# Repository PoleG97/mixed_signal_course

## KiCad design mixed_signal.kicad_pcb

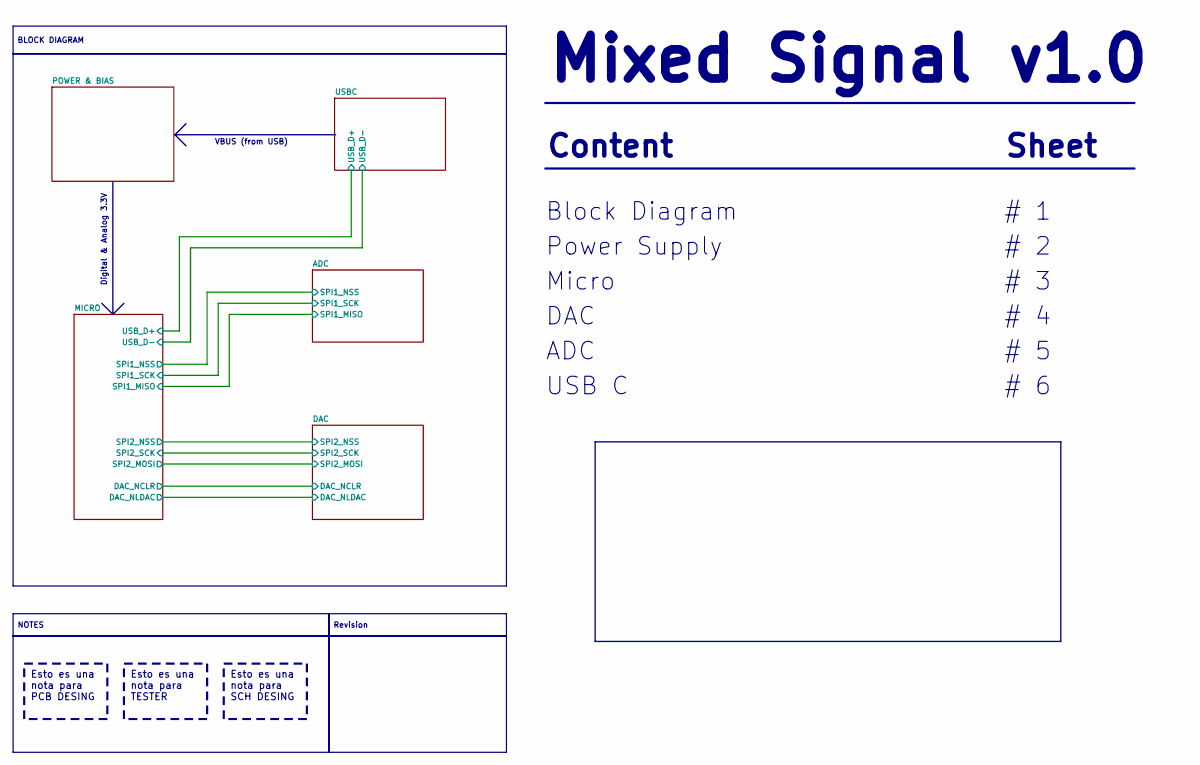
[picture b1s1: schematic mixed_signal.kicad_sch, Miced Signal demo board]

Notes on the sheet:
Micro
# 2
ADC
# 4
Power Supply
# 3
# 1
Content
USB C
v1.0
# 5
VBUS (from USB)
Block Diagram
Mixed Signal
DAC
Digital & Analog 3.3V
# 6
Sheet
Esto es una nota para TESTER
NOTES
Esto es una nota para SCH DESING
BLOCK DIAGRAM
Esto es una nota para PCB DESING
Revision

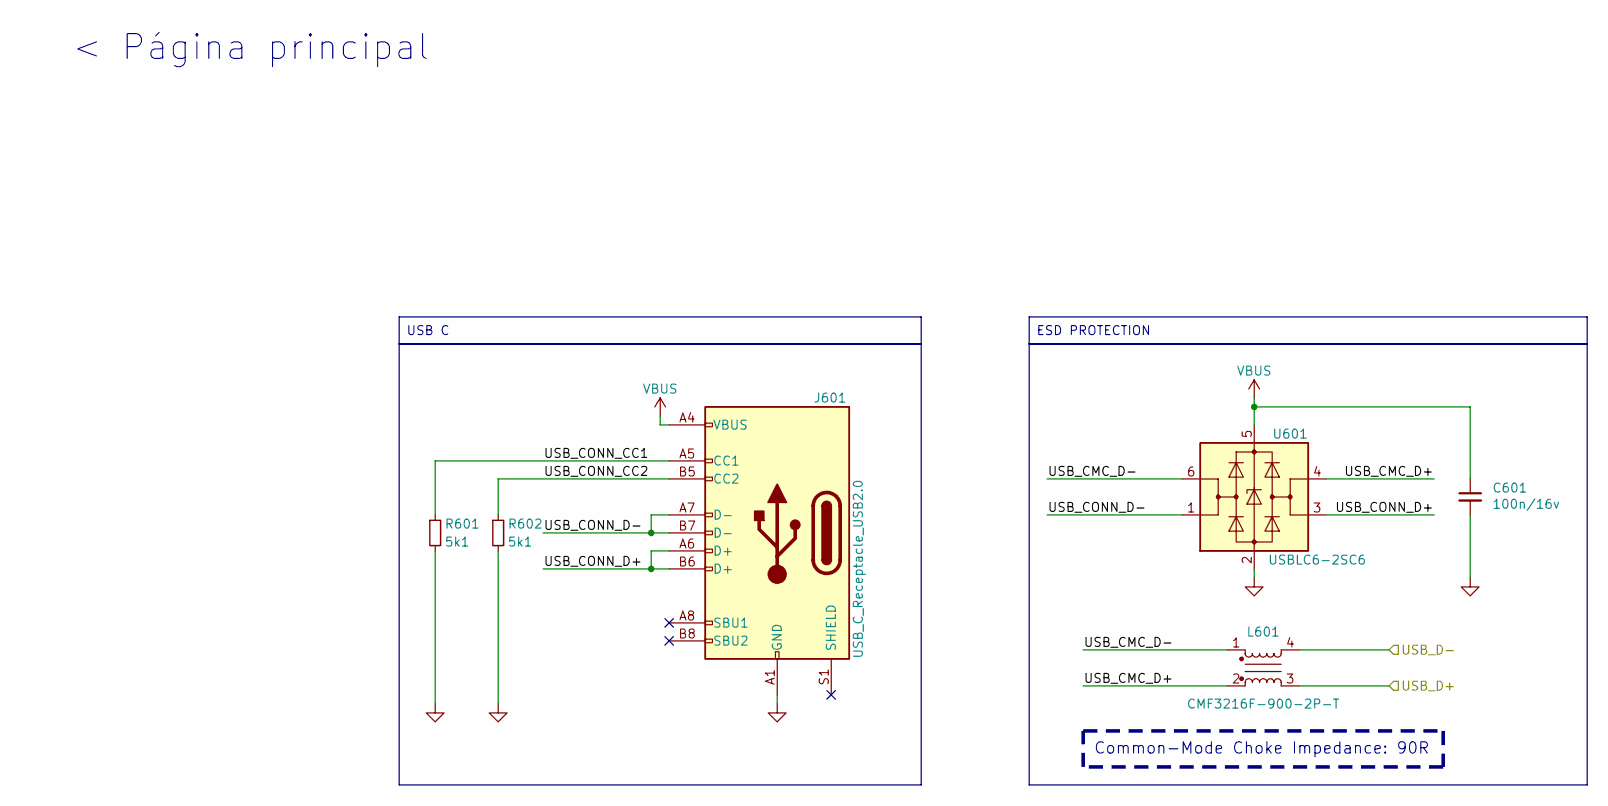
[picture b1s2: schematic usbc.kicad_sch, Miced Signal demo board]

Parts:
C601: 100n/16v; C_0402_1005Metric_Pad0.74x0.62mm_HandSolder; PART_NUMBER GRM155R71C104KA88J
J601: USB_C_Receptacle_USB2.0; USB_C_Receptacle_HRO_TYPE-C-31-M-12
L601: CMF3216F-900-2P-T; CMF3216F
R601, R602: 5k1; R_0402_1005Metric
U601: USBLC6-2SC6; SOT-23-6

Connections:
/MICRO/USB_D+: L601.3; also elsewhere on the board
/MICRO/USB_D-: L601.4; also elsewhere on the board
/USBC/USB_CMC_D+: L601.2, U601.4 (I/O2)
/USBC/USB_CMC_D-: L601.1, U601.6 (I/O1)
/USBC/USB_CONN_CC1: J601.A5 (CC1), R601.1
/USBC/USB_CONN_CC2: J601.B5 (CC2), R602.1
/USBC/USB_CONN_D+: J601.A6 (D+), J601.B6 (D+), U601.3 (I/O2)
/USBC/USB_CONN_D-: J601.A7 (D-), J601.B7 (D-), U601.1 (I/O1)
GND: C601.2, J601.A1 (GND), J601.A12 (GND), J601.B1 (GND), J601.B12 (GND), R601.2, R602.2, U601.2 (GND); also elsewhere on the board
VBUS: C601.1, J601.A4 (VBUS), J601.A9 (VBUS), J601.B4 (VBUS), J601.B9 (VBUS), U601.5 (VBUS); also elsewhere on the board

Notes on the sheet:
Common-Mode Choke Impedance: 90R
< Página principal
ESD PROTECTION
USB C

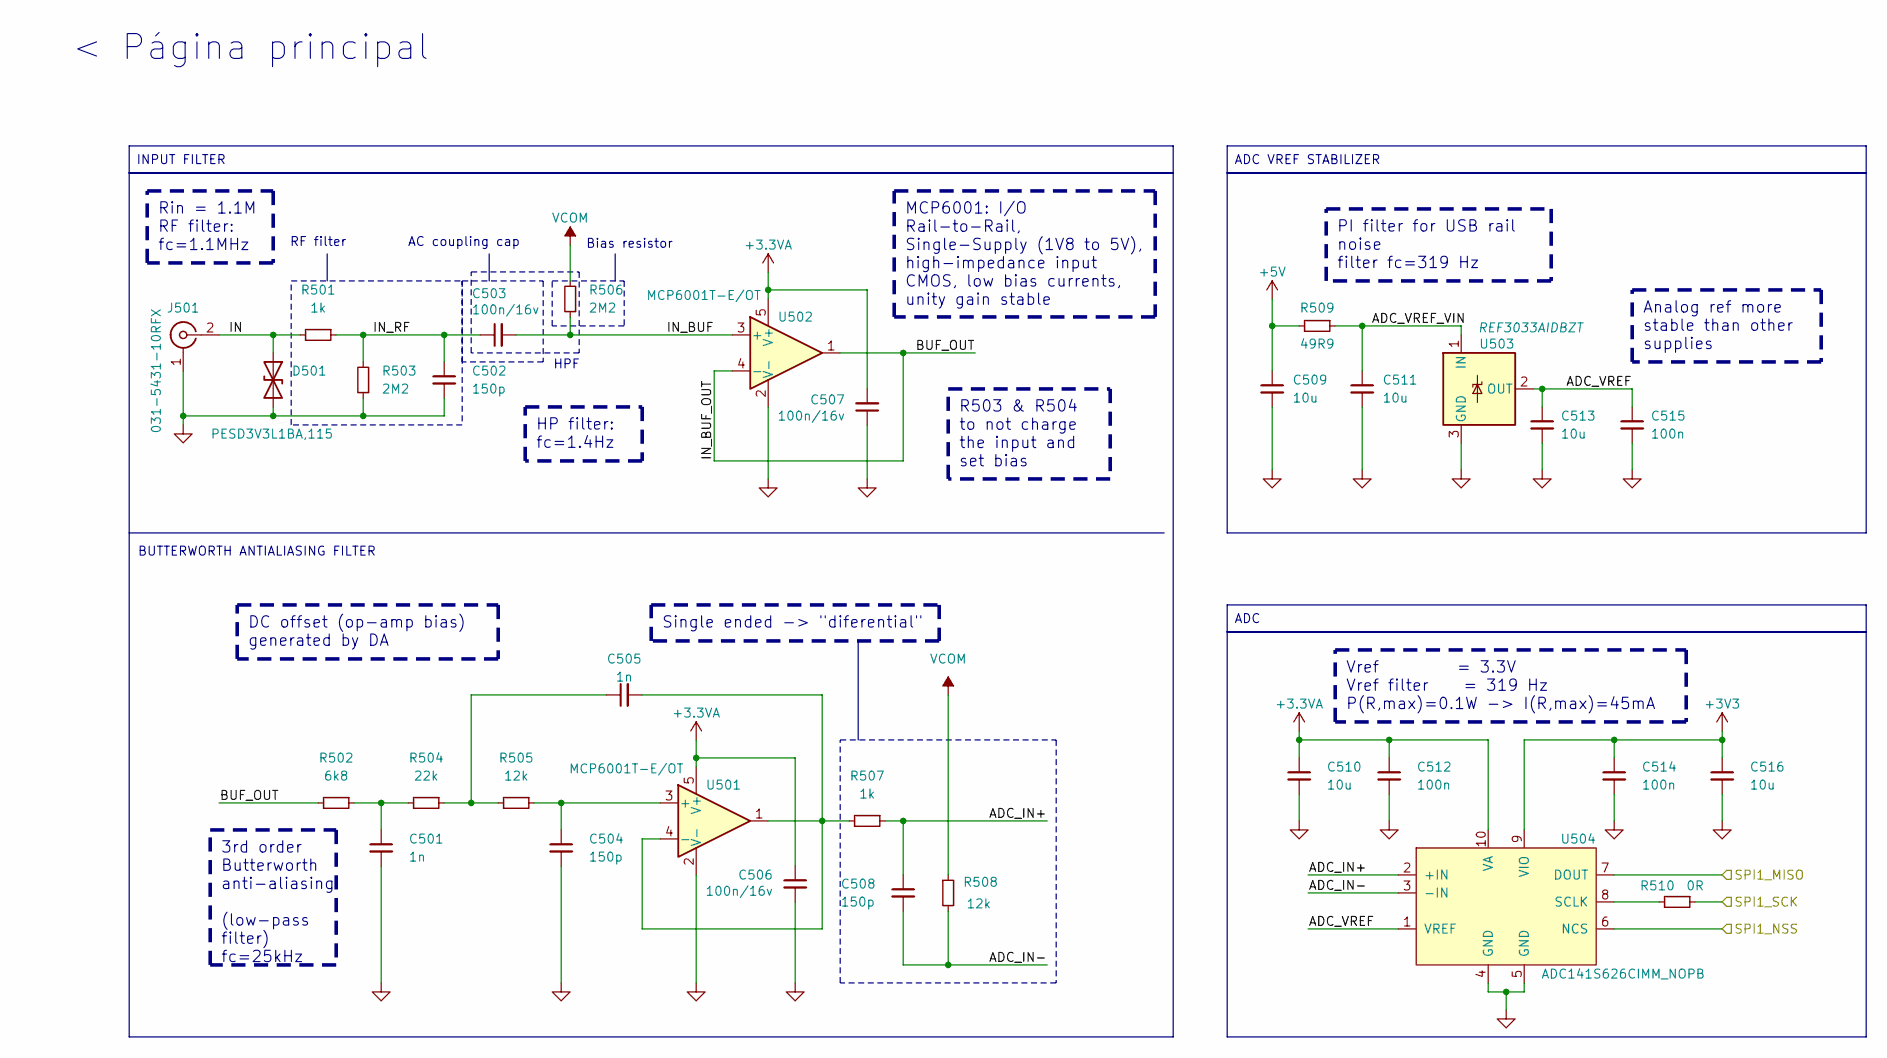
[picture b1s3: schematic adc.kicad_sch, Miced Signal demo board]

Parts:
C501, C505: 1n; C_0402_1005Metric
C502, C504, C508: 150p; C_0402_1005Metric
C503, C506, C507: 100n/16v; C_0402_1005Metric_Pad0.74x0.62mm_HandSolder; PART_NUMBER GRM155R71C104KA88J
C509, C510, C511, C513, C516: 10u; C_0603_1608Metric
C512, C514, C515: 100n; C_0402_1005Metric
D501: PESD3V3L1BA,115; D_SOD-323
J501: 031-5431-10RFX
R501, R507: 1k; R_0402_1005Metric
R502: 6k8; R_0402_1005Metric
R503, R506: 2M2; R_0402_1005Metric
R504: 22k; R_0402_1005Metric
R505, R508: 12k; R_0402_1005Metric
R509: 49R9; R_0402_1005Metric
R510: 0R; R_0402_1005Metric
U501, U502: MCP6001T-E/OT; SOT-23-5
U503: REF3033AIDBZT; SOT-23
U504: ADC141S626CIMM_NOPB; VSSOP-10

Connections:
+3.3VA: C506.1, C507.2, C510.1, C512.1, U501.5 (V+), U502.5 (V+), U504.10 (VA); also elsewhere on the board
+3V3: C514.1, C516.1, U504.9 (VIO); also elsewhere on the board
+5V: C509.1, R509.2; also elsewhere on the board
/ADC/ADC_IN+: C508.1, R507.1, U504.2 (+IN)
/ADC/ADC_IN-: C508.2, R508.2, U504.3 (-IN)
/ADC/ADC_VREF: C513.1, C515.1, U503.2 (OUT), U504.1 (VREF)
/ADC/ADC_VREF_VIN: C511.1, R509.1, U503.1 (IN)
/ADC/BUF_OUT: R502.2, U502.1, U502.4 (-)
/ADC/IN: D501.1 (A1), J501.2 (Ext), R501.2
/ADC/IN_BUF: C503.2, R506.1, U502.3 (+)
/ADC/IN_RF: C502.1, C503.1, R501.1, R503.2
/ADC/SPI1_MISO: U504.7 (DOUT); also elsewhere on the board
/ADC/SPI1_NSS: U504.6 (NCS); also elsewhere on the board
/ADC/SPI1_SCK: R510.1; also elsewhere on the board
GND: C501.2, C502.2, C504.2, C506.2, C507.1, C509.2, C510.2, C511.2, C512.2, C513.2, C514.2, C515.2, C516.2, D501.2 (A2), J501.1 (In), R503.1, U501.2 (V-), U502.2 (V-), U503.3 (GND), U504.4 (GND), U504.5 (GND); also elsewhere on the board
unnamed: C501.1, R502.1, R504.2
unnamed: C505.1, R504.1, R505.2
unnamed: C504.1, R505.1, U501.3 (+)
unnamed: C505.2, R507.2, U501.1, U501.4 (-)
unnamed: R510.2, U504.8 (SCLK)
VCOM: R506.2, R508.1; also elsewhere on the board

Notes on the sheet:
RF filter
AC coupling cap
HPF
BUTTERWORTH ANTIALIASING FILTER
Bias resistor
ADC
Vref = 3.3V Vref filter = 319 Hz P(R,max)=0.1W -> I(R,max)=45mA
HP filter: fc=1.4Hz
INPUT FILTER
ADC VREF STABILIZER
Single ended -> "diferential"
MCP6001: I/O Rail-to-Rail, Single-Supply (1V8 to 5V), high-impedance input CMOS, low bias currents, unity gain stable
PI filter for USB rail noise filter fc=319 Hz
Rin = 1.1M RF filter: fc=1.1MHz
DC offset (op-amp bias) generated by DA
3rd order Butterworth anti-aliasing (low-pass filter) fc=25kHz
Analog ref more stable than other supplies
R503 & R504 to not charge the input and set bias
< Página principal

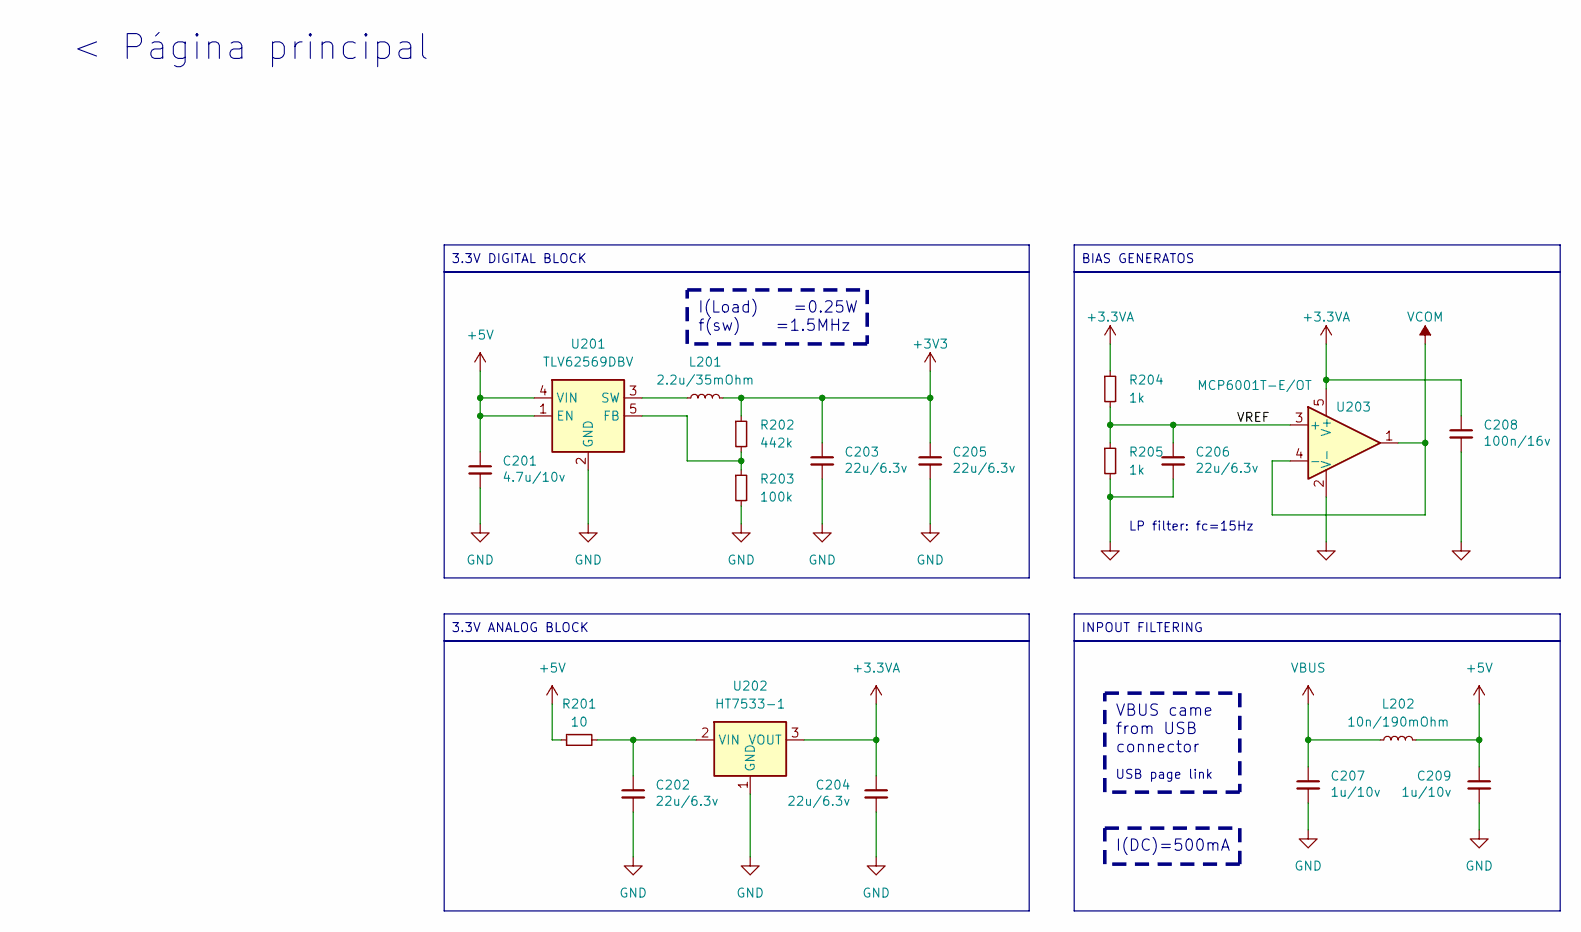
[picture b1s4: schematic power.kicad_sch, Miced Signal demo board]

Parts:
C201: 4.7u/10v; C_0402_1005Metric_Pad0.74x0.62mm_HandSolder; PART_NUMBER C1005X5R1A475K050BC
C202, C203, C204, C205, C206: 22u/6.3v; C_0402_1005Metric_Pad0.74x0.62mm_HandSolder; PART_NUMBER GRJ155R60J106ME11D
C207, C209: 1u/10v; C_0402_1005Metric_Pad0.74x0.62mm_HandSolder; PART_NUMBER CL05B104KP5NNNC
C208: 100n/16v; C_0402_1005Metric_Pad0.74x0.62mm_HandSolder; PART_NUMBER GRM155R71C104KA88J
L201: 2.2u/35mOhm; IND_ASPI-0530HI-2R2M-T2; PART_NUMBER ASPI-0530HI-2R2M-T2
L202: 10n/190mOhm; L_0402_1005Metric_Pad0.77x0.64mm_HandSolder; PART_NUMBER LQG15WZ10NH02D
R201: 10; R_1206_3216Metric_Pad1.30x1.75mm_HandSolder; PART_NUMBER Susumu
R202: 442k; R_0402_1005Metric
R203: 100k; R_0402_1005Metric
R204, R205: 1k; R_0402_1005Metric; PART_NUMBER ERJ-2RKF1001X
U201: TLV62569DBV; SOT-23-5
U202: HT7533-1; SOT-89-3
U203: MCP6001T-E/OT; SOT-23-5; PART_NUMBER MCP6001T-E/OT

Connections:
+3.3VA: C204.1, C208.1, R204.1, U202.3 (VOUT), U203.5 (V+); also elsewhere on the board
+3V3: C203.1, C205.1, L201.2, R202.1; also elsewhere on the board
+5V: C201.1, C209.1, L202.2, R201.1, U201.1 (EN), U201.4 (VIN); also elsewhere on the board
/POWER & BIAS/VREF: C206.1, R204.2, R205.1, U203.3 (+)
GND: C201.2, C202.2, C203.2, C204.2, C205.2, C206.2, C207.2, C208.2, C209.2, R203.2, R205.2, U201.2 (GND), U202.1 (GND), U203.2 (V-); also elsewhere on the board
unnamed: R202.2, R203.1, U201.5 (FB)
unnamed: L201.1, U201.3 (SW)
unnamed: C202.1, R201.2, U202.2 (VIN)
VBUS: C207.1, L202.1; also elsewhere on the board
VCOM: U203.1, U203.4 (-); also elsewhere on the board

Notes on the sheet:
LP filter: fc=15Hz
USB page link
3.3V DIGITAL BLOCK
< Página principal
BIAS GENERATOS
3.3V ANALOG BLOCK
VBUS came from USB connector
I(DC)=500mA
INPOUT FILTERING
I(Load) =0.25W f(sw) =1.5MHz

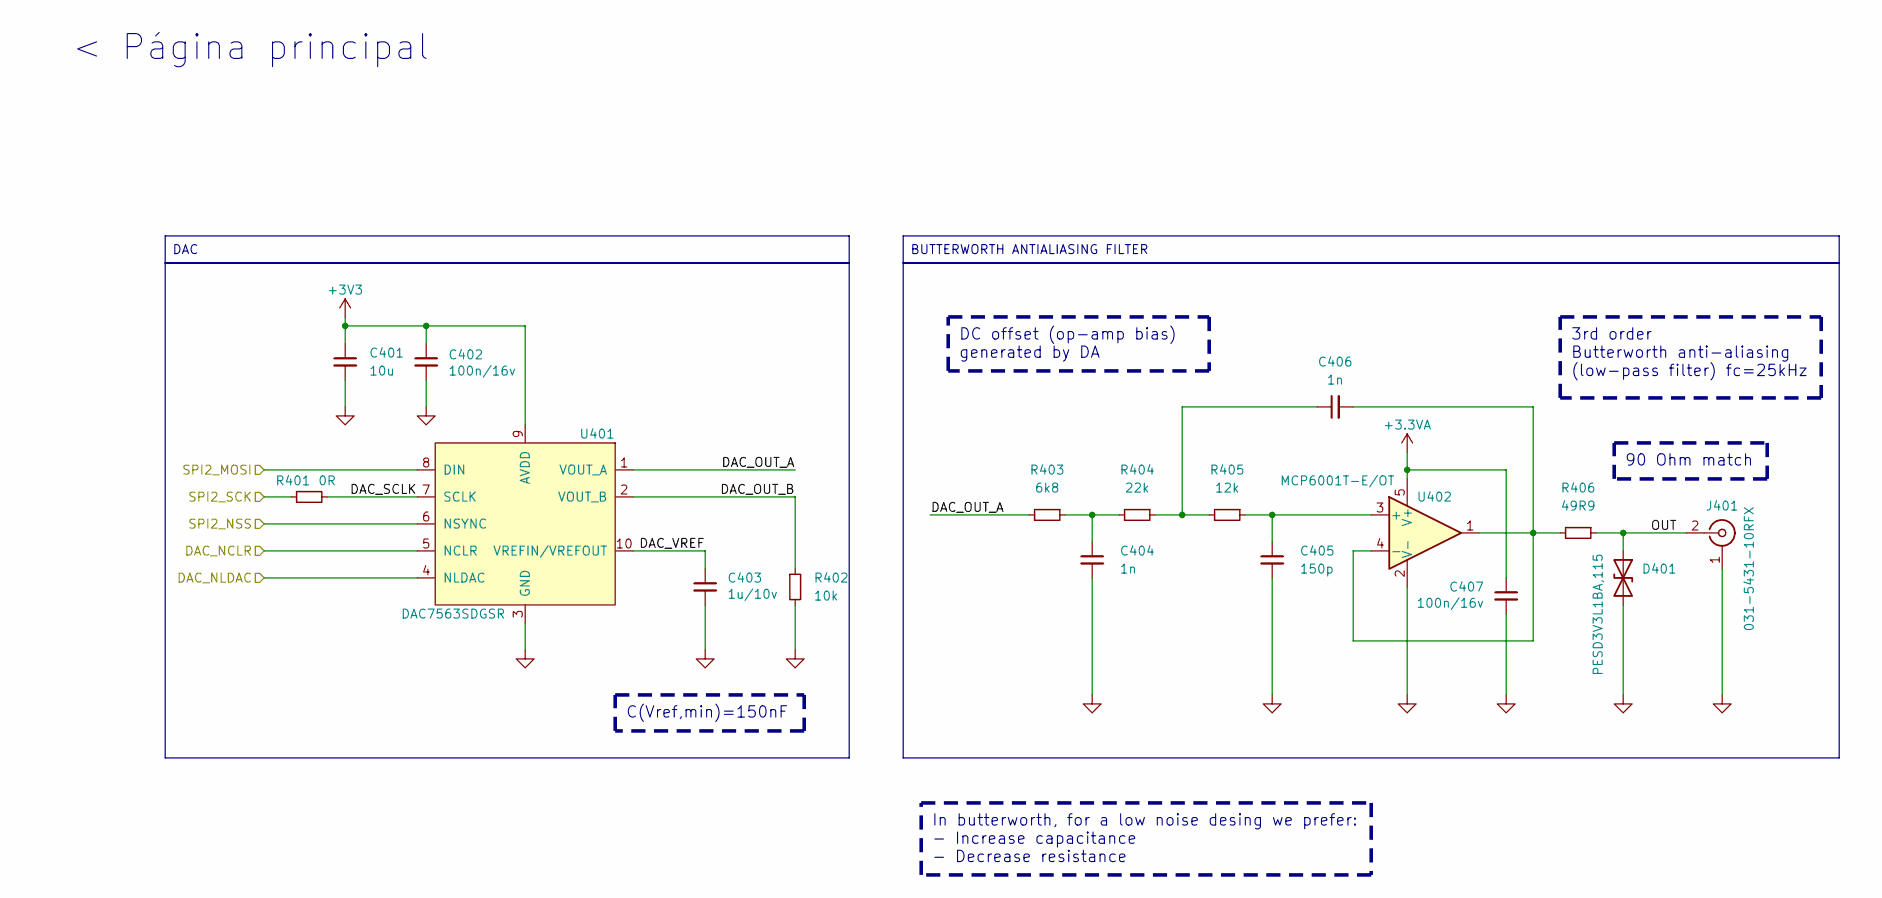
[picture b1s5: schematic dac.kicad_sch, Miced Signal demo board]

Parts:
C401: 10u; C_0603_1608Metric
C402, C407: 100n/16v; C_0402_1005Metric_Pad0.74x0.62mm_HandSolder; PART_NUMBER GRM155R71C104KA88J
C403: 1u/10v; C_0402_1005Metric_Pad0.74x0.62mm_HandSolder; PART_NUMBER CL05B104KP5NNNC
C404, C406: 1n; C_0402_1005Metric
C405: 150p; C_0402_1005Metric
D401: PESD3V3L1BA,115; D_SOD-323
J401: 031-5431-10RFX
R401: 0R; R_0402_1005Metric
R402: 10k; R_0402_1005Metric
R403: 6k8; R_0402_1005Metric
R404: 22k; R_0402_1005Metric
R405: 12k; R_0402_1005Metric
R406: 49R9; R_0402_1005Metric
U401: DAC7563SDGSR; VSSOP-10
U402: MCP6001T-E/OT; SOT-23-5

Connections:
+3.3VA: C407.1, U402.5 (V+); also elsewhere on the board
+3V3: C401.1, C402.1, U401.9 (AVDD); also elsewhere on the board
/DAC/DAC_NCLR: U401.5 (NCLR); also elsewhere on the board
/DAC/DAC_NLDAC: U401.4 (NLDAC); also elsewhere on the board
/DAC/DAC_OUT_A: R403.2, U401.1 (VOUT_A)
/DAC/DAC_OUT_B: R402.1, U401.2 (VOUT_B)
/DAC/DAC_SCLK: R401.2, U401.7 (SCLK)
/DAC/DAC_VREF: C403.1, U401.10 (VREFIN/VREFOUT)
/DAC/OUT: D401.1 (A1), J401.2 (Ext), R406.1
/DAC/SPI2_MOSI: U401.8 (DIN); also elsewhere on the board
/DAC/SPI2_NSS: U401.6 (NSYNC); also elsewhere on the board
/DAC/SPI2_SCK: R401.1; also elsewhere on the board
GND: C401.2, C402.2, C403.2, C404.2, C405.2, C407.2, D401.2 (A2), J401.1 (In), R402.2, U401.3 (GND), U402.2 (V-); also elsewhere on the board
unnamed: C404.1, R403.1, R404.2
unnamed: C406.1, R404.1, R405.2
unnamed: C405.1, R405.1, U402.3 (+)
unnamed: C406.2, R406.2, U402.1, U402.4 (-)

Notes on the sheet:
< Página principal
DAC
In butterworth, for a low noise desing we prefer: - Increase capacitance - Decrease resistance
C(Vref,min)=150nF
DC offset (op-amp bias) generated by DA
BUTTERWORTH ANTIALIASING FILTER
90 Ohm match
3rd order Butterworth anti-aliasing (low-pass filter) fc=25kHz

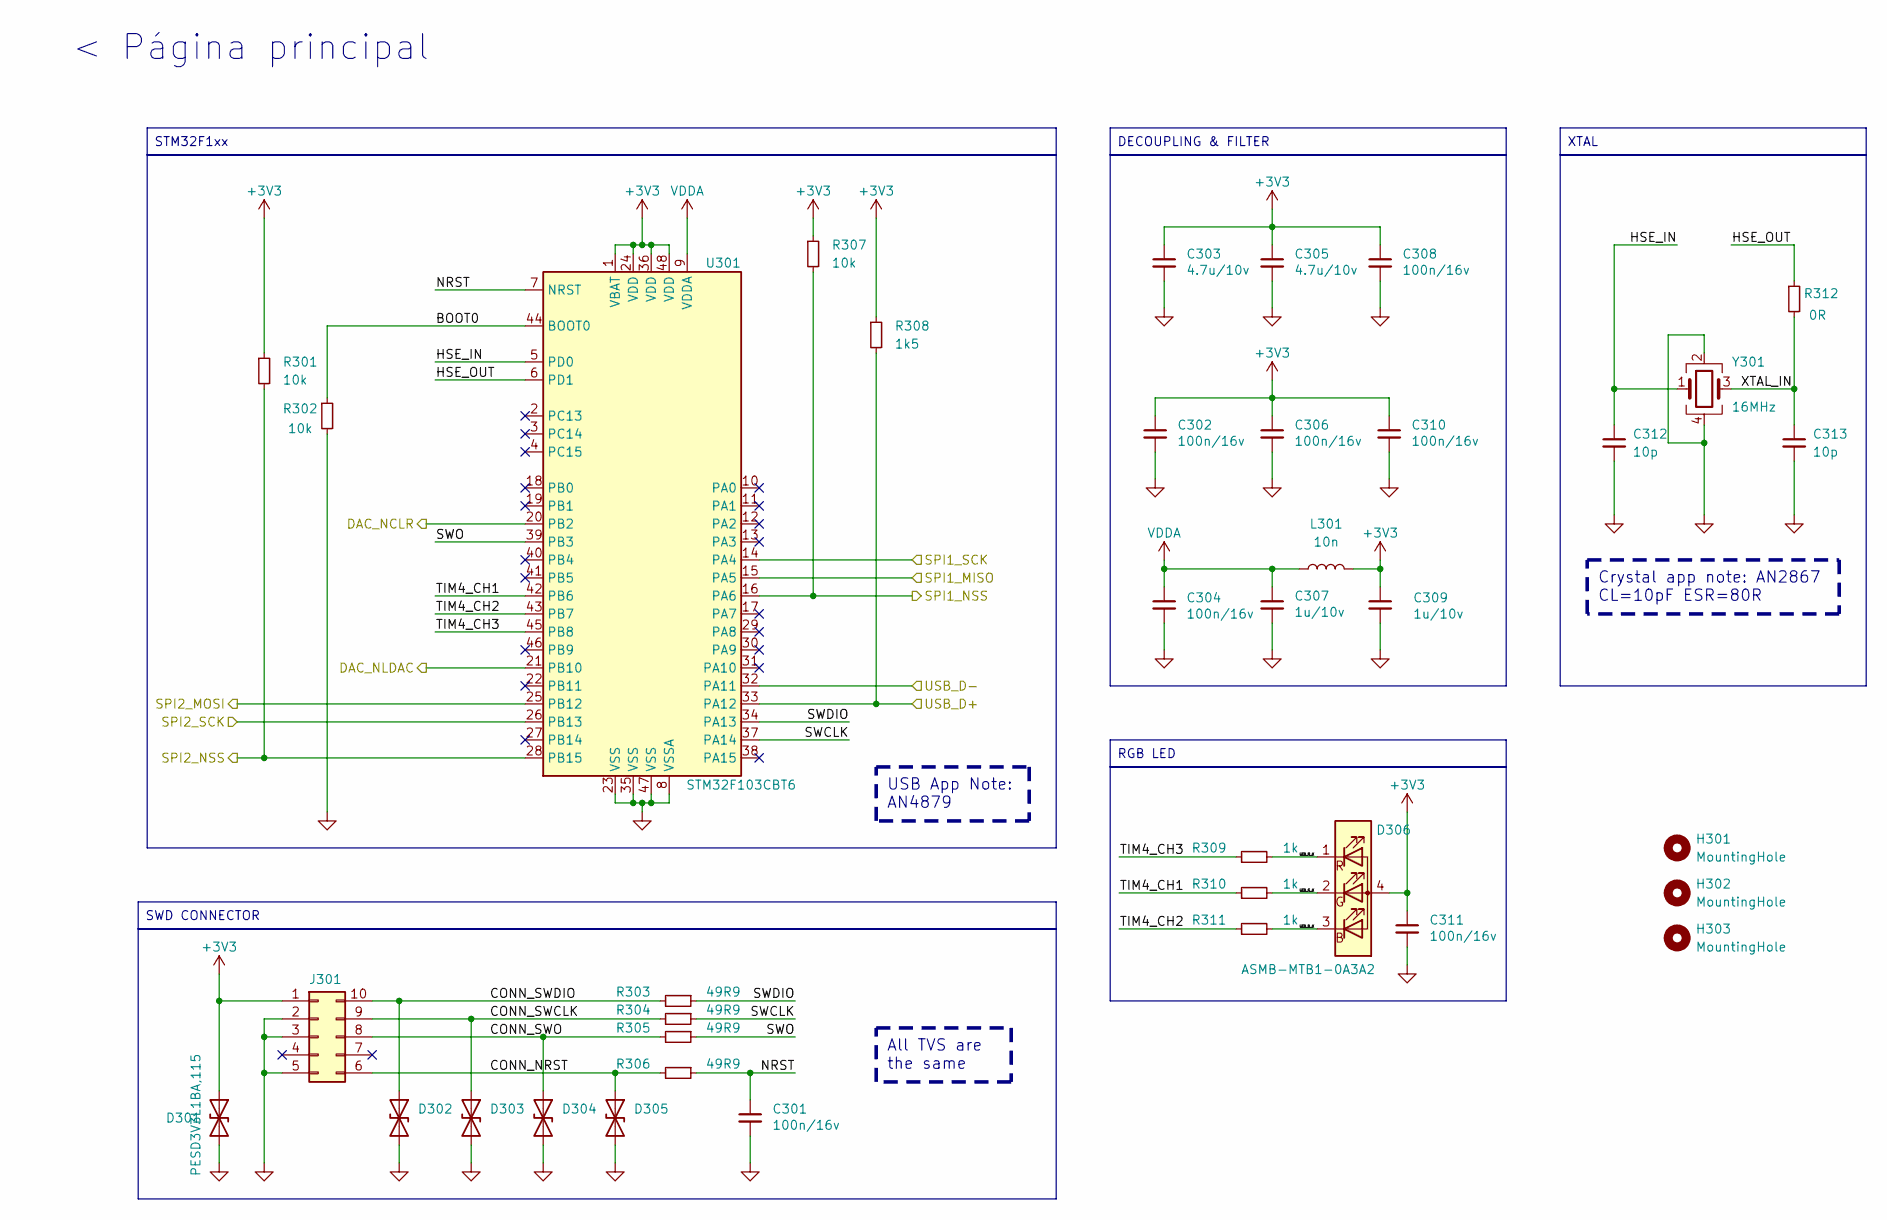
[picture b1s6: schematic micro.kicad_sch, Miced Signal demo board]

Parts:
C301, C302, C304, C306, C308, C310, C311: 100n/16v; C_0402_1005Metric_Pad0.74x0.62mm_HandSolder; PART_NUMBER GRM155R71C104KA88J
C303, C305: 4.7u/10v; C_0402_1005Metric_Pad0.74x0.62mm_HandSolder; PART_NUMBER C1005X5R1A475K050BC
C307, C309: 1u/10v; C_0402_1005Metric_Pad0.74x0.62mm_HandSolder; PART_NUMBER CL05B104KP5NNNC
C312, C313: 10p; C_0402_1005Metric
D301, D302, D303, D304, D305: PESD3V3L1BA,115; D_SOD-323
D306: ASMB-MTB1-0A3A2; LED_Avago_PLCC4_3.2x2.8mm_CW
H301, H302, H303: MountingHole; MountingHole_3.2mm_M3
J301: Conn_02x05_Counter_Clockwise; PinHeader_2x05_P1.27mm_Vertical_SMD
L301: 10n; L_0402_1005Metric
R301, R302, R307: 10k; R_0402_1005Metric
R303, R304, R305, R306: 49R9; R_0402_1005Metric
R308: 1k5; R_0402_1005Metric
R309, R310, R311: 1k; R_0402_1005Metric
R312: 0R; R_0402_1005Metric
U301: STM32F103CBT6; LQFP-48_7x7mm_P0.5mm; Manufacturer Part Number STM32F103CBT6
Y301: 16MHz; Crystal_SMD_3225-4Pin_3.2x2.5mm

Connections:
+3V3: C302.1, C303.1, C305.1, C306.1, C308.1, C309.1, C310.1, C311.1, D301.1 (A1), D306.4 (A), J301.1, L301.2, R301.1, R307.1, R308.1, U301.1 (VBAT), U301.24 (VDD), U301.36 (VDD), U301.48 (VDD); also elsewhere on the board
/ADC/SPI1_MISO: U301.15 (PA5); also elsewhere on the board
/ADC/SPI1_NSS: R307.2, U301.16 (PA6); also elsewhere on the board
/ADC/SPI1_SCK: U301.14 (PA4); also elsewhere on the board
/DAC/DAC_NCLR: U301.20 (PB2); also elsewhere on the board
/DAC/DAC_NLDAC: U301.21 (PB10); also elsewhere on the board
/DAC/SPI2_MOSI: U301.25 (PB12); also elsewhere on the board
/DAC/SPI2_NSS: R301.2, U301.28 (PB15); also elsewhere on the board
/DAC/SPI2_SCK: U301.26 (PB13); also elsewhere on the board
/MICRO/BOOT0: R302.1, U301.44 (BOOT0)
/MICRO/CONN_NRST: D305.1 (A1), J301.6, R306.2
/MICRO/CONN_SWCLK: D303.1 (A1), J301.9, R304.2
/MICRO/CONN_SWDIO: D302.1 (A1), J301.10, R303.2
/MICRO/CONN_SWO: D304.1 (A1), J301.8, R305.2
/MICRO/HSE_IN: C312.1, U301.5 (PD0), Y301.1
/MICRO/HSE_OUT: R312.1, U301.6 (PD1)
/MICRO/LED_B_K: D306.3 (BK), R311.2
/MICRO/LED_G_K: D306.2 (GK), R310.2
/MICRO/LED_R_K: D306.1 (RK), R309.2
/MICRO/NRST: C301.1, R306.1, U301.7 (NRST)
/MICRO/SWCLK: R304.1, U301.37 (PA14)
/MICRO/SWDIO: R303.1, U301.34 (PA13)
/MICRO/SWO: R305.1, U301.39 (PB3)
/MICRO/TIM4_CH1: R310.1, U301.42 (PB6)
/MICRO/TIM4_CH2: R311.1, U301.43 (PB7)
/MICRO/TIM4_CH3: R309.1, U301.45 (PB8)
/MICRO/USB_D+: R308.2, U301.33 (PA12); also elsewhere on the board
/MICRO/USB_D-: U301.32 (PA11); also elsewhere on the board
/MICRO/XTAL_IN: C313.1, R312.2, Y301.3
GND: C301.2, C302.2, C303.2, C304.2, C305.2, C306.2, C307.2, C308.2, C309.2, C310.2, C311.2, C312.2, C313.2, D301.2 (A2), D302.2 (A2), D303.2 (A2), D304.2 (A2), D305.2 (A2), J301.2, J301.3, J301.5, R302.2, U301.8 (VSSA), U301.23 (VSS), U301.35 (VSS), U301.47 (VSS), Y301.2, Y301.4; also elsewhere on the board
VDDA: C304.1, C307.1, L301.1, U301.9 (VDDA)

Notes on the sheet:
USB App Note: AN4879
< Página principal
Crystal app note: AN2867 CL=10pF ESR=80R
SWD CONNECTOR
DECOUPLING & FILTER
All TVS are the same
RGB LED
XTAL
STM32F1xx

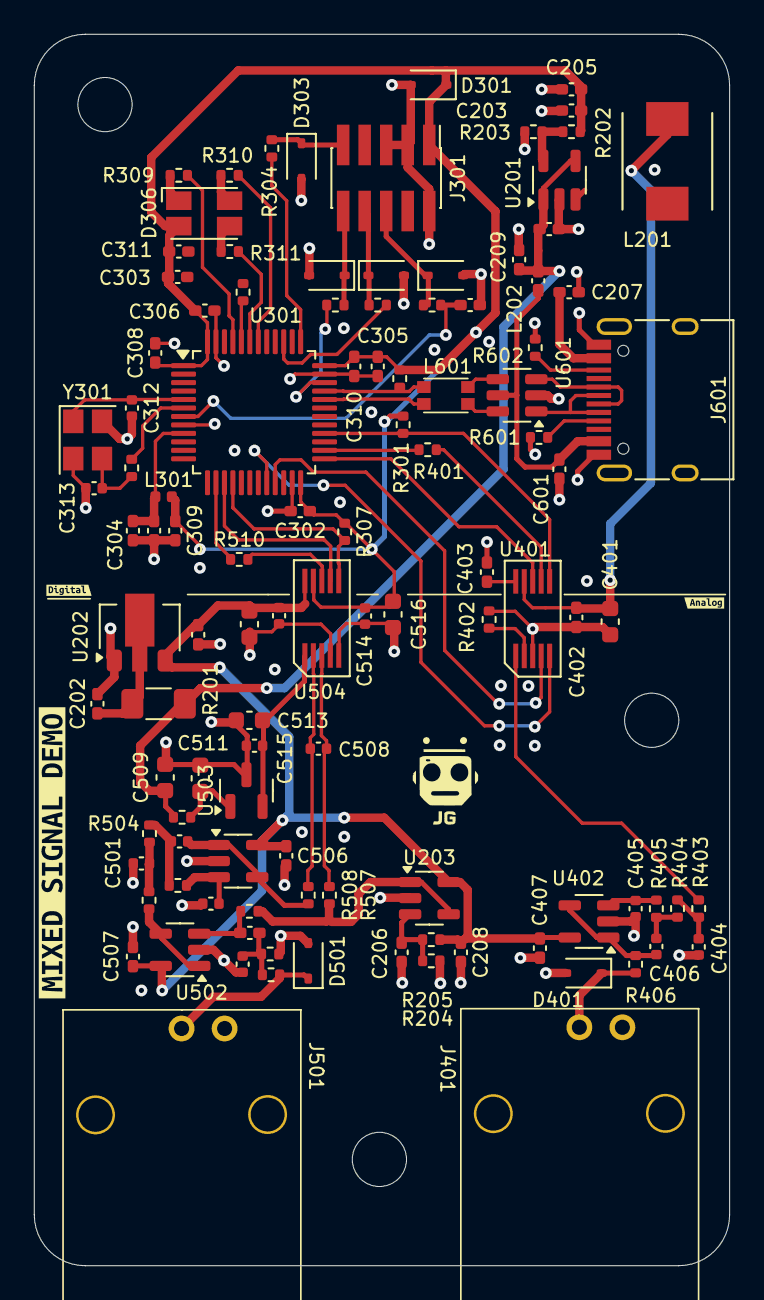
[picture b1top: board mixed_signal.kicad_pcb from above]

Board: 4 copper layers, 41.0 x 72.7 mm, 115 parts (0 on the bottom side), 67 nets.

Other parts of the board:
kibuzzard-67B740F3: G***; kibuzzard-67B740F3
kibuzzard-67B741FF: G***; kibuzzard-67B741FF
kibuzzard-67B74215: G***; kibuzzard-67B74215

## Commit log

2025-03-20 Inicializado
